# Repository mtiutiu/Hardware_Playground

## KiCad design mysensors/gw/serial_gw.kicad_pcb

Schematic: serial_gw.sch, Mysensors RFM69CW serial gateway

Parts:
C1, C2, C3, C4, C6, C7, C9, C12, C14: 100n; C_0603_HandSoldering
C8, C10, C11: 1u; C_0603_HandSoldering
C13: 22u; C_0603_HandSoldering
CON1: AVR-ISP-6; AVR_ISP_SMT_Small_02x03
D1: RX; LED_0603
D2: TX; LED_0603
D3: ERR; LED_0603
IC1: ATMEGA328P-MU; QFN-32-1EP_5x5mm_Pitch0.5mm
P1: USB_A
P2: ANTENNA; Pin_Header_Straight_1x01_Pitch2.00mm
R1: 10K; R_0603_HandSoldering
R2, R3, R4: 330; R_0603_HandSoldering
R5: 56K; R_0603_HandSoldering
R6: 1K; R_0603_HandSoldering
SW1: RESET; SW_SPST_EVQPE1
U1: TXB0104; TSSOP-14_4.4x5mm_Pitch0.65mm
U2: MCP1703A-3302; SOT89-3_Housing
U3: CP2102; QFN-28-1EP_5x5mm_Pitch0.5mm
U4: RFM69W; RFM69HW_SMD_Handsoldering
U5: ATSHA204A; SOT-23
X1: 16MHz; ZTTCS-3

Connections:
+3V3: C9.2, C11.1, C13.1, R5.2, U1.1, U1.8, U2.3, U4.8 (3.3V)
+5V: C1.1, C2.2, C3.2, C7.1, C8.1, C10.2, C14.1, CON1.2, IC1.4, IC1.6, IC1.18, P1.1, R1.1, R6.2, U1.14, U2.2, U3.7, U3.8, U5.2
/ATSHA204A: IC1.26, R6.1, U5.1
/DTR: C6.2, U3.28
/GW_ERR_LED: IC1.25, R4.2
/GW_RX_LED: IC1.23, R2.2
/GW_TX_LED: IC1.24, R3.2
/MISO: CON1.1, IC1.16, U1.11
/MOSI: CON1.4, IC1.15, U1.12
/RFM69W_INT: IC1.32, U4.2 (DIO0)
/RFM69W_SS: IC1.14, U1.13
/RST: C6.1, CON1.5, IC1.29, R1.2, SW1.1
/SCK: CON1.3, IC1.17, U1.10
/SER_RX: IC1.31, U3.25
/SER_TX: IC1.30, U3.26
GND: C1.2, C2.1, C3.1, C4.1, C7.2, C8.2, C9.1, C10.1, C11.2, C12.2, C13.2, C14.2, CON1.6, D1.1, D2.1, D3.1, IC1.3, IC1.5, IC1.21, P1.4, P1.5, SW1.2, U1.7, U2.1, U3.3, U4.9 (GND), U4.11 (GND), U5.3, X1.2
unnamed: C4.2, IC1.20
unnamed: C12.1, U3.6
unnamed: D1.2, R2.1
unnamed: D2.2, R3.1
unnamed: D3.2, R4.1
unnamed: IC1.7, X1.3
unnamed: IC1.8, X1.1
unnamed: P1.2, U3.5
unnamed: P1.3, U3.4
unnamed: P2.1, U4.10 (ANA)
unnamed: R5.1, U1.2, U4.15 (NSS)
unnamed: U1.3, U4.14 (MOSI)
unnamed: U1.4, U4.13 (MISO)
unnamed: U1.5, U4.12 (SCK)

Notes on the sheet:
Usb to serial converter
RFM69W radio module
3.3V supply
AVR ISP
LED panel
MCU unit
Signing module

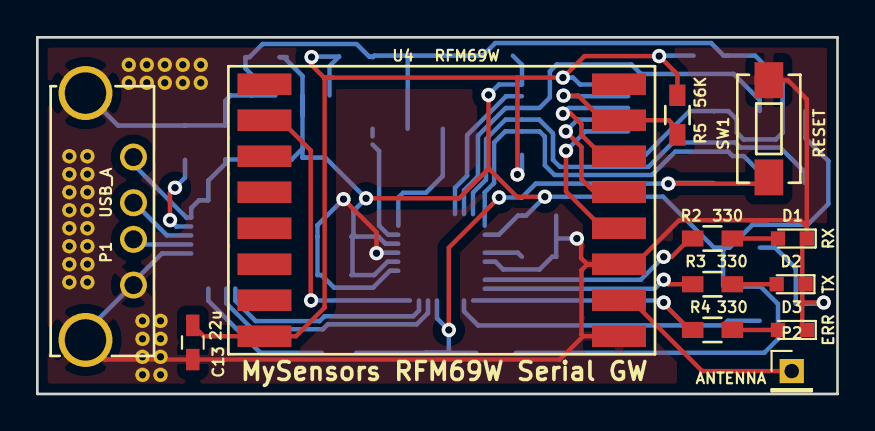
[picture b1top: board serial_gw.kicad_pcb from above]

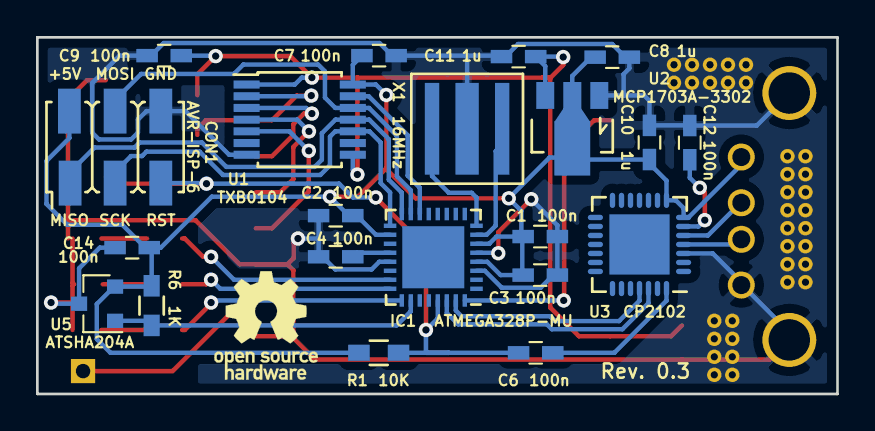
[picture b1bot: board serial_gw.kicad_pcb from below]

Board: 2 copper layers, 44.5 x 19.8 mm, 33 parts (21 on the bottom side), 30 nets.

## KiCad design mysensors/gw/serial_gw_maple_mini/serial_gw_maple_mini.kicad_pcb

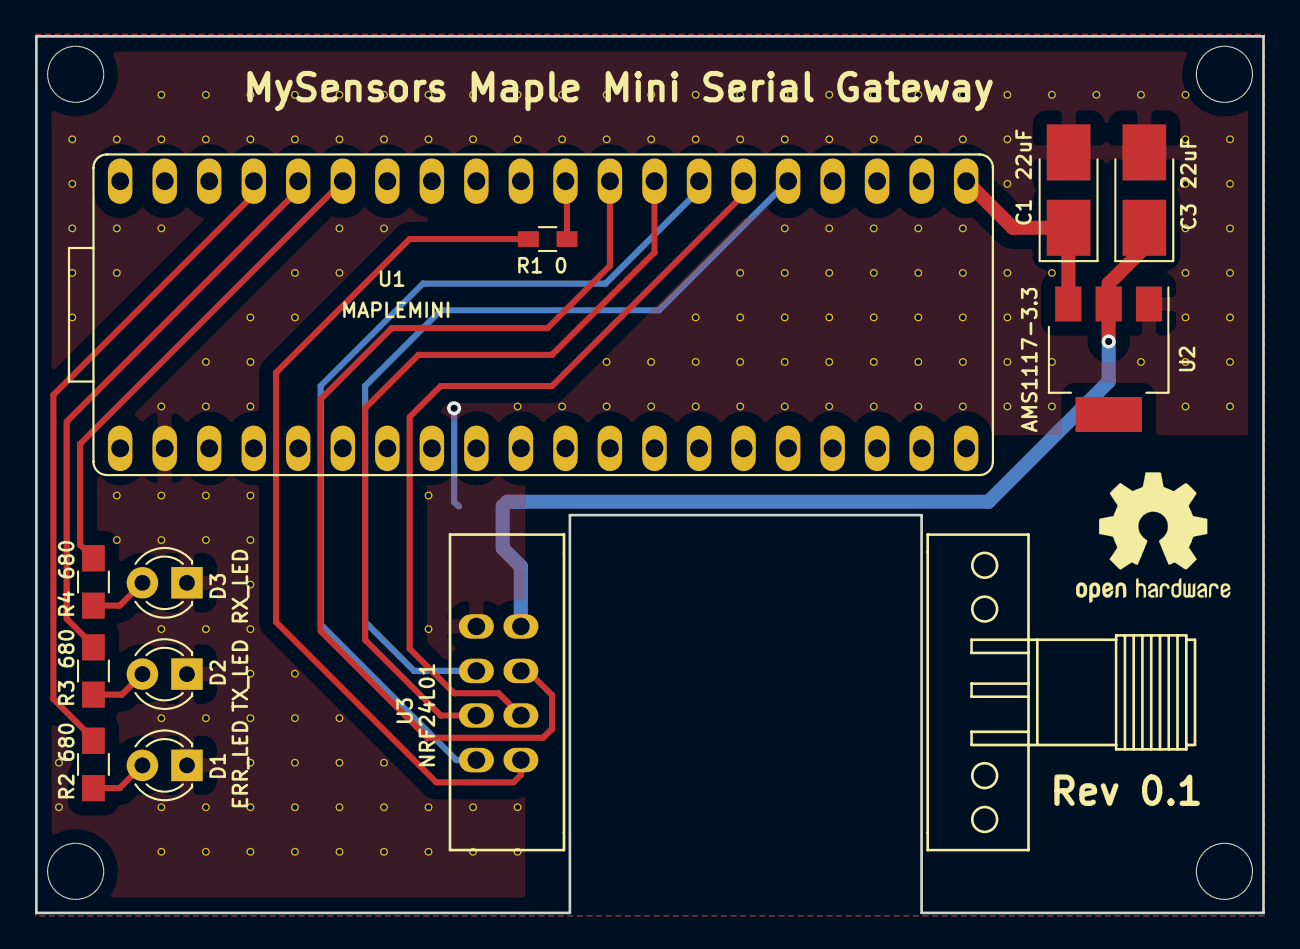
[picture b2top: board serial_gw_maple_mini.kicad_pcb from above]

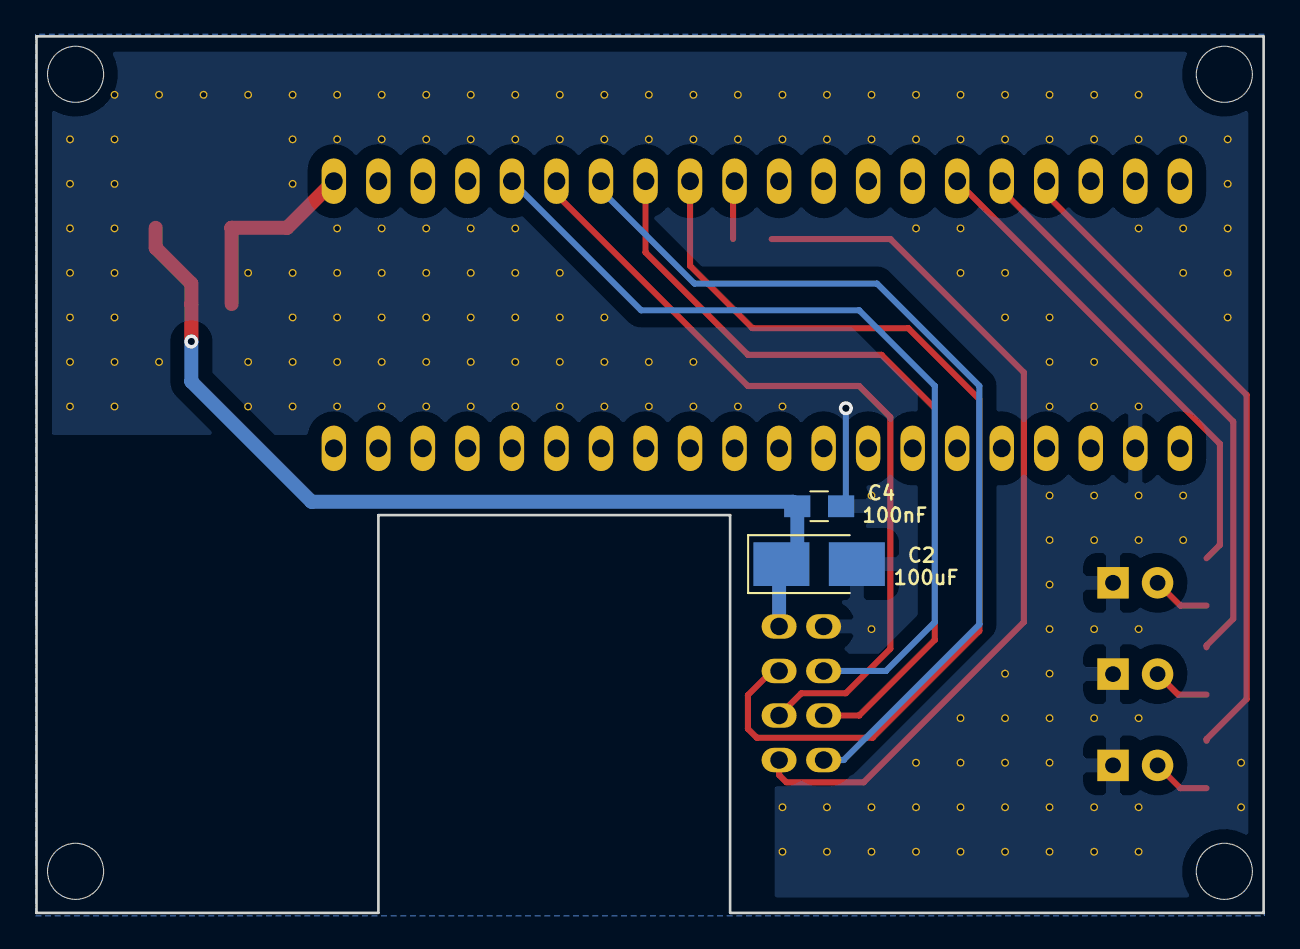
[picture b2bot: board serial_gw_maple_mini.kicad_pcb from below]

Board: 2 copper layers, 70.0 x 50.0 mm, 184 parts (2 on the bottom side), 16 nets.

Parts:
C1, C3: 22uF; CP_Tantalum_Case-B_EIA-3528-21_Hand
C2: 100uF; CP_Tantalum_Case-B_EIA-3528-21_Hand
C4: 100nF; C_0805_HandSoldering
D1: ERR_LED; LED_D3.0mm
D2: TX_LED; LED_D3.0mm
D3: RX_LED; LED_D3.0mm
R1: 0; R_0603_HandSoldering
R2, R3, R4: 680; R_0805_HandSoldering
U1: MAPLEMINI; MAPLE_MINI
U2: AMS1117-3.3; SOT-223
U3: NRF24L01; E01-ML01DP5
V3_4, V3_5, V3_6, V3_7, V3_8, V3_18, V3_19, V4_4, V4_6, V4_7, V4_12, V4_13, V5_3, V5_4, V5_6, V5_10, V5_12, V5_13, V5_15, V5_17, V5_19, V5_20, V6_3, V6_4, V6_9, V6_10, V6_12, V6_13, V6_15, V6_17, V6_19, V6_20, V7_3, V7_4, V7_8, V7_9, V7_10, V7_12, V7_13, V7_14, V7_15, V7_16, V7_17, V7_18, V7_19, V7_20, V8_3, V8_4, V8_7, V8_8, V8_16, V8_17, V8_18, V8_19, V8_20, V9_3, V9_4, V9_6, V9_7, V9_17, V9_18, V9_19, V9_20, V10_3, V10_4, V10_6, V10_18, V10_19, V10_20, V11_3, V11_4, V11_12, V11_15, V11_19, V11_20, V12_3, V12_4, V12_19, V12_20, V13_3, V13_4, V13_10, V13_19, V13_20, V14_3, V14_4, V14_10, V15_3, V15_4, V15_9, V15_10, V16_3, V16_4, V16_9, V16_10, V17_3, V17_4, V17_8, V17_9, V17_10, V18_3, V18_4, V18_7, V18_8, V18_9, V18_10, V19_3, V19_4, V19_6, V19_7, V19_8, V19_9, V19_10, V20_3, V20_4, V20_6, V20_7, V20_8, V20_9, V20_10, V21_3, V21_4, V21_6, V21_7, V21_8, V21_9, V21_10, V22_3, V22_4, V22_6, V22_7, V22_8, V22_9, V22_10, V23_3, V23_4, V23_6, V23_7, V23_8, V23_9, V23_10, V24_3, V24_4, V24_5, V24_7, V24_8, V24_9, V24_10, V25_3, V25_7, V25_9, V25_10, V26_3, V27_3, V27_9, V28_3, V28_4, V28_5, V28_6, V28_7, V28_8, V28_9, V28_10, V29_4, V29_5, V29_6, V29_7, V29_8, V29_9, V29_10: AUTO_VIA; VIA_MATRIX

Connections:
+3V3: C2.1, C3.1, C4.1, U2.2, U3.2
/ERR_LED: R2.2, U1.37
/MAPLE_VIN: C1.1, U1.21, U2.3
/NRF24_IRQ: R1.1, U3.8
/RX_LED: R4.2, U1.35
/SPI_CE: U1.25, U3.3
/SPI_CSN: U1.29, U3.4
/SPI_MISO: U1.27, U3.7
/SPI_MOSI: U1.26, U3.6
/SPI_SCK: U1.28, U3.5
/TX_LED: R3.2, U1.36
GND: C1.2, C2.2, C3.2, C4.2, D1.1, D2.1, D3.1, U1.2, U2.1, U3.1, V3_4.1, V3_5.1, V3_6.1, V3_7.1, V3_8.1, V3_18.1, V3_19.1, V4_4.1, V4_6.1, V4_7.1, V4_12.1, V4_13.1, V5_3.1, V5_4.1, V5_6.1, V5_10.1, V5_12.1, V5_13.1, V5_15.1, V5_17.1, V5_19.1, V5_20.1, V6_3.1, V6_4.1, V6_9.1, V6_10.1, V6_12.1, V6_13.1, V6_15.1, V6_17.1, V6_19.1, V6_20.1, V7_3.1, V7_4.1, V7_8.1, V7_9.1, V7_10.1, V7_12.1, V7_13.1, V7_14.1, V7_15.1, V7_16.1, V7_17.1, V7_18.1, V7_19.1, V7_20.1, V8_3.1, V8_4.1, V8_7.1, V8_8.1, V8_16.1, V8_17.1, V8_18.1, V8_19.1, V8_20.1, V9_3.1, V9_4.1, V9_6.1, V9_7.1, V9_17.1, V9_18.1, V9_19.1, V9_20.1, V10_3.1, V10_4.1, V10_6.1, V10_18.1, V10_19.1, V10_20.1, V11_3.1, V11_4.1, V11_12.1, V11_15.1, V11_19.1, V11_20.1, V12_3.1, V12_4.1, V12_19.1, V12_20.1, V13_3.1, V13_4.1, V13_10.1, V13_19.1, V13_20.1, V14_3.1, V14_4.1, V14_10.1, V15_3.1, V15_4.1, V15_9.1, V15_10.1, V16_3.1, V16_4.1, V16_9.1, V16_10.1, V17_3.1, V17_4.1, V17_8.1, V17_9.1, V17_10.1, V18_3.1, V18_4.1, V18_7.1, V18_8.1, V18_9.1, V18_10.1, V19_3.1, V19_4.1, V19_6.1, V19_7.1, V19_8.1, V19_9.1, V19_10.1, V20_3.1, V20_4.1, V20_6.1, V20_7.1, V20_8.1, V20_9.1, V20_10.1, V21_3.1, V21_4.1, V21_6.1, V21_7.1, V21_8.1, V21_9.1, V21_10.1, V22_3.1, V22_4.1, V22_6.1, V22_7.1, V22_8.1, V22_9.1, V22_10.1, V23_3.1, V23_4.1, V23_6.1, V23_7.1, V23_8.1, V23_9.1, V23_10.1, V24_3.1, V24_4.1, V24_5.1, V24_7.1, V24_8.1, V24_9.1, V24_10.1, V25_3.1, V25_7.1, V25_9.1, V25_10.1, V26_3.1, V27_3.1, V27_9.1, V28_3.1, V28_4.1, V28_5.1, V28_6.1, V28_7.1, V28_8.1, V28_9.1, V28_10.1, V29_4.1, V29_5.1, V29_6.1, V29_7.1, V29_8.1, V29_9.1, V29_10.1
unnamed: D1.2, R2.1
unnamed: D2.2, R3.1
unnamed: D3.2, R4.1
unnamed: R1.2, U1.30

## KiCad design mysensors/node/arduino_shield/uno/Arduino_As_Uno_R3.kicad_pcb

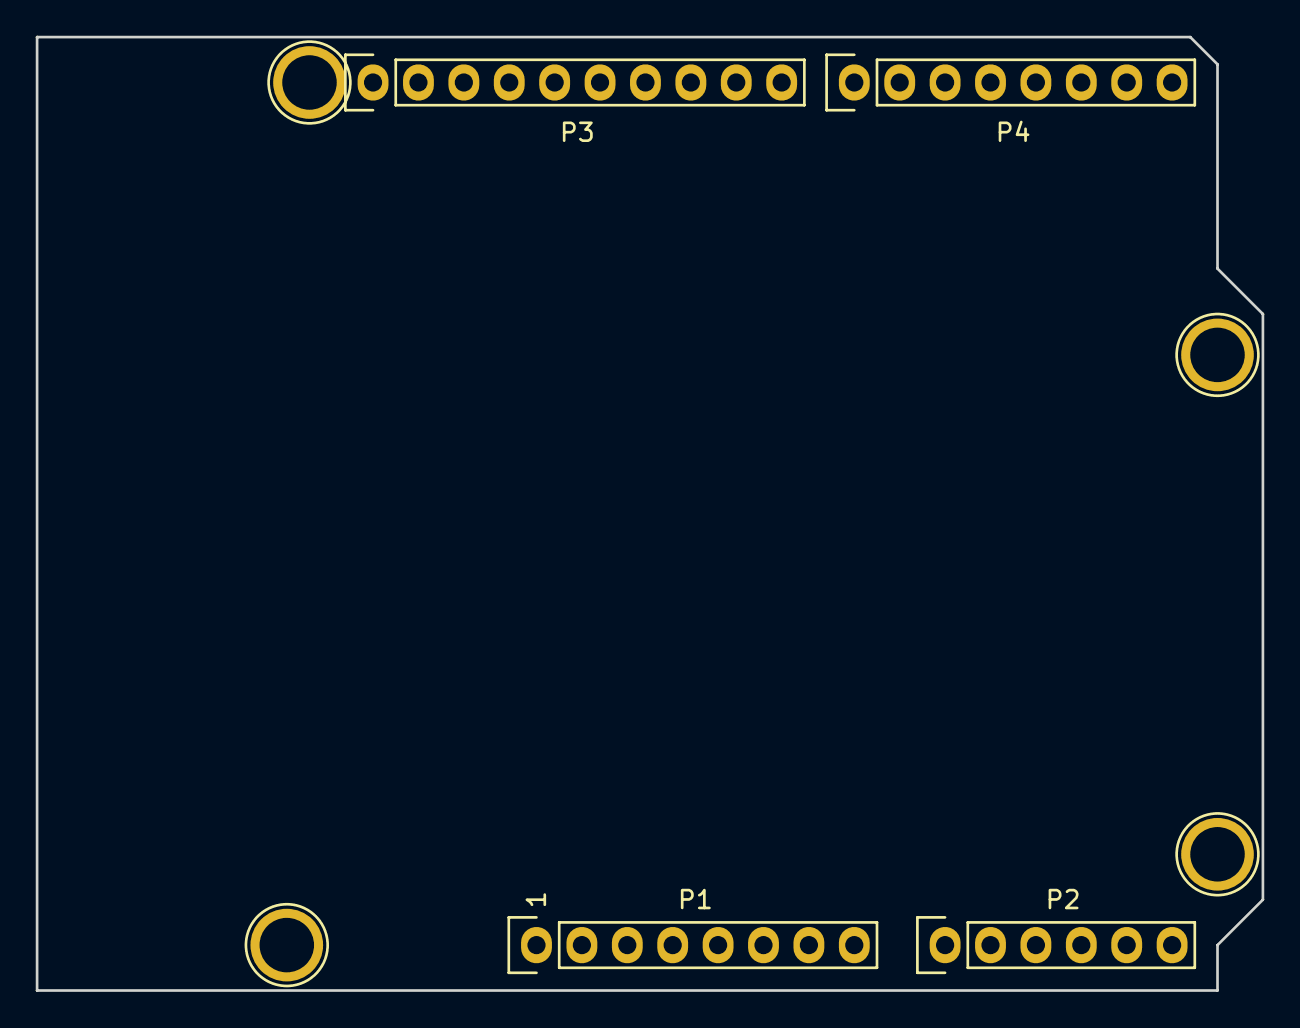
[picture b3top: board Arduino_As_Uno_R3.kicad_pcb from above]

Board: 2 copper layers, 68.6 x 53.3 mm, 8 parts (0 on the bottom side), 3 nets, no tracks yet.

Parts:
P1: Power; Socket_Strip_Arduino_1x08
P2: Analog; Socket_Strip_Arduino_1x06
P3: Digital; Socket_Strip_Arduino_1x10
P4: Digital; Socket_Strip_Arduino_1x08
P5, P6, P7, P8: CONN_01X01; Arduino_1pin

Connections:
/A4(SDA): P2.5, P3.2
/A5(SCL): P2.6, P3.1
GND: P1.6, P1.7, P3.4

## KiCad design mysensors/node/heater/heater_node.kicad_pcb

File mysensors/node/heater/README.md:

## Mysensors RFM69W heater relay module
More details here: https://www.openhardware.io/view/334/MySensors-RFM69W-relay-actuator-node

##### 3D renderings of pcb

Top view | Bottom view
------------ | -------------
 | 

**Description:**

This is a Mysensors RFM69W actuator node for controlling a heater or other appliances using a relay

**Key Features:**

 - **AT25DF512C-SSHN-B** SPI flash module for OTA
 - **ATSHA204A** for signing
 - **MySensors** ready(Atmega328p + RFM69W)
 - **HLK-PM01** as power supply

**Work progress:**

 1. Test/verify the pcb board correctness(from both electrical and mechanical point of views) - **DONE**
 2. Produce the initial PCB's using some external PCB manufacturer - **DONE**
 3. Components assembly(soldering) -**DONE**
 4. Create 3D printed plastic enclosure - **DONE**
 5. Create MySensors sketch code - **DONE**
 6. Verify the real board with running code - **DONE**

**HW Revisions:**
 - 0.1 - initial hw design
 - 0.2 - removed capacitor from reset switch as it can interfere with arduino serial bootloader if used

**Credits:**
  
  All credits go to **MySensors** team for the great work and to the opensource community

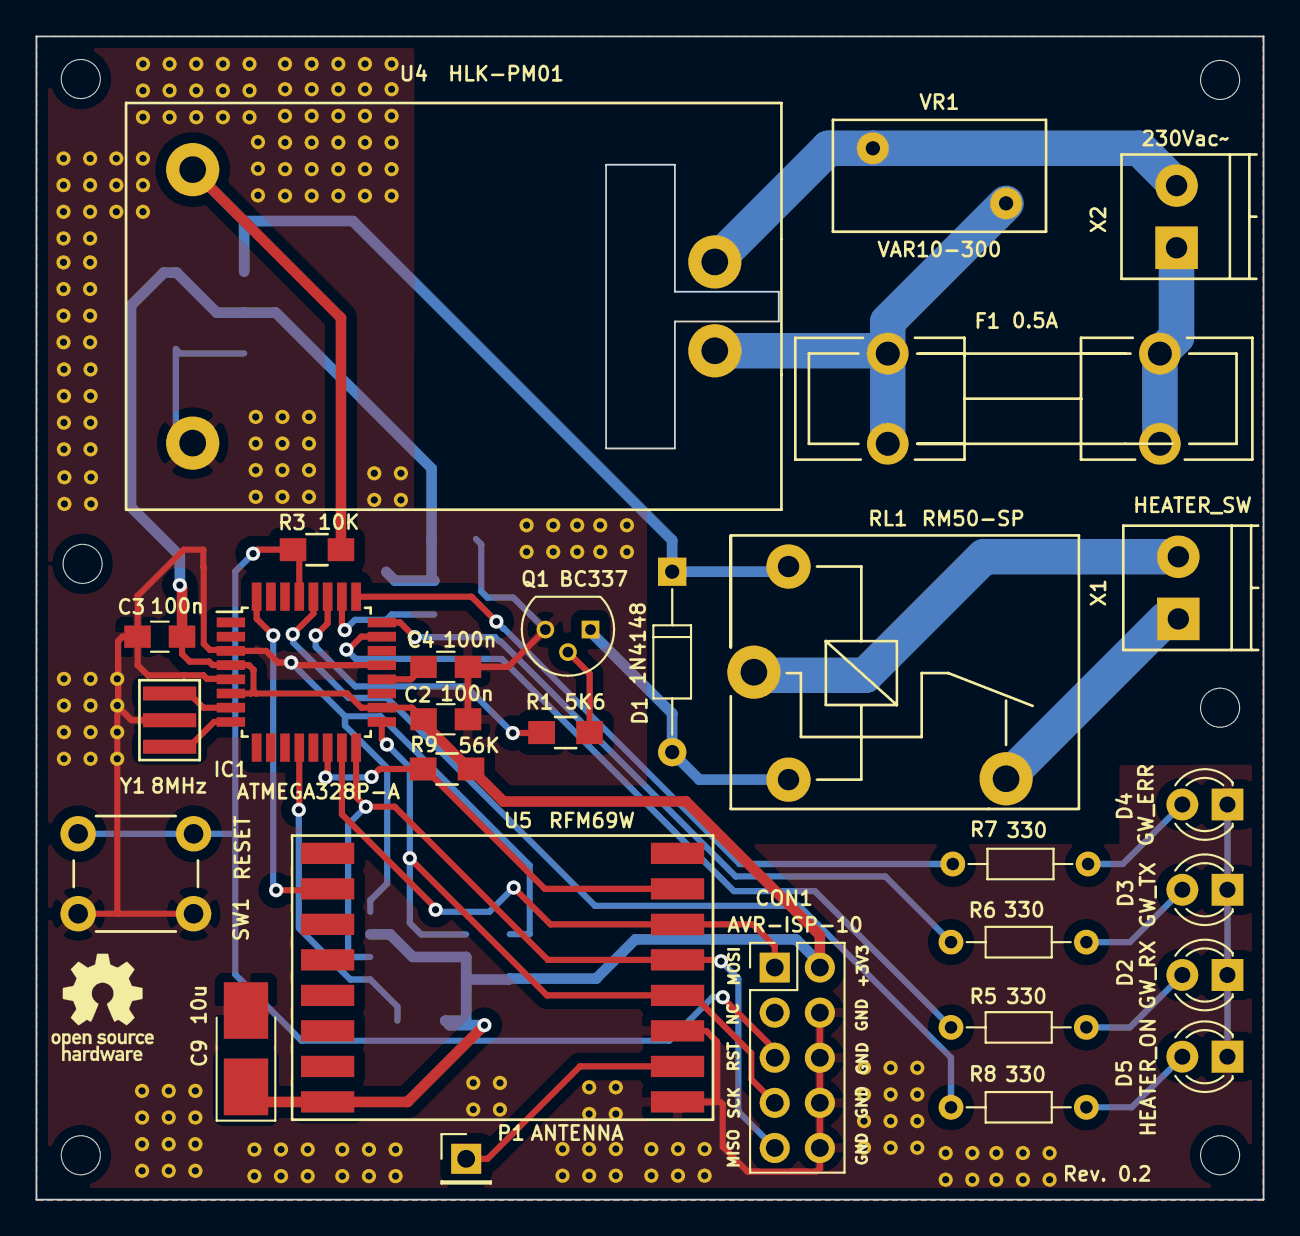
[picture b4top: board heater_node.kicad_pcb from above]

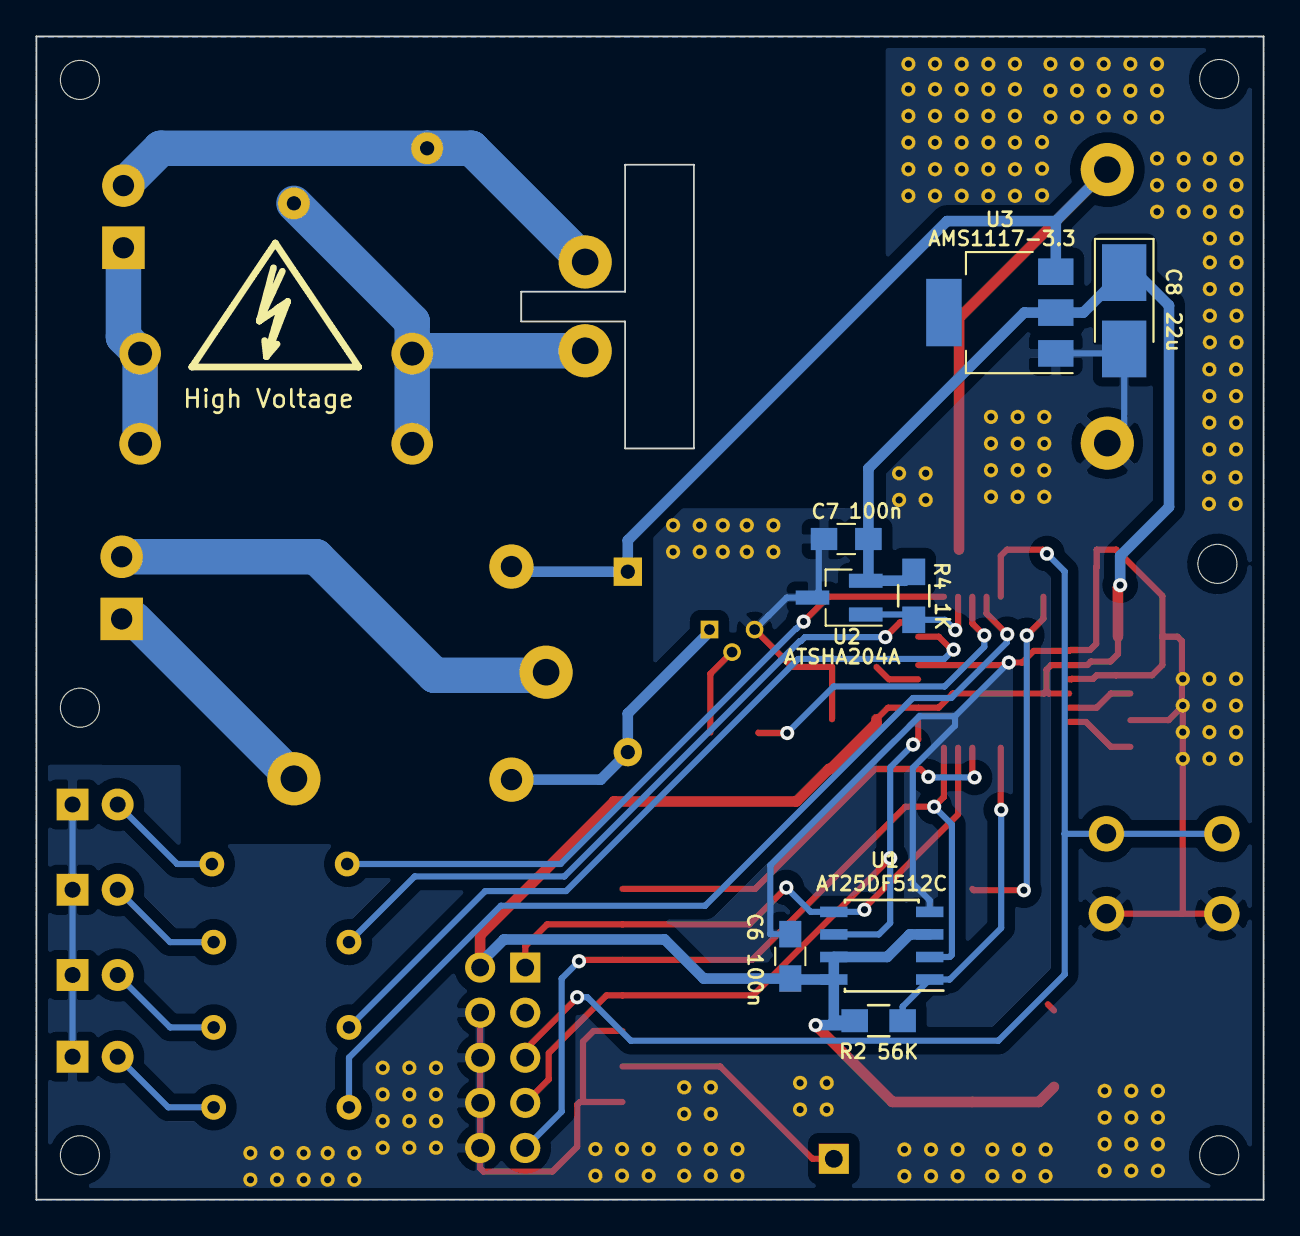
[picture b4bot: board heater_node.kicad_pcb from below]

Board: 2 copper layers, 69.1 x 65.5 mm, 37 parts (8 on the bottom side), 31 nets.

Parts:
C2, C3, C4, C6, C7: 100n; C_0805_HandSoldering
C8: 22u; CP_Tantalum_Case-B_EIA-3528-21_Hand
C9: 10u; CP_Tantalum_Case-B_EIA-3528-21_Hand
CON1: AVR-ISP-10; Pin_Header_Straight_2x05_Pitch2.54mm
D1: 1N4148; D_DO-35_SOD27_P10.16mm_Horizontal
D2: GW_RX; LED_D3.0mm
D3: GW_TX; LED_D3.0mm
D4: GW_ERR; LED_D3.0mm
D5: HEATER_ON; LED_D3.0mm
F1: 0.5A; Fuseholder5x20_horiz_open_lateral_Type-II
IC1: ATMEGA328P-A; TQFP-32_7x7mm_Pitch0.8mm
P1: ANTENNA; Pin_Header_Straight_1x01_Pitch2.54mm
Q1: BC337; TO-92_Molded_Narrow
R1: 5K6; R_0805_HandSoldering
R2, R9: 56K; R_0805_HandSoldering
R3: 10K; R_0805_HandSoldering
R4: 1K; R_0805_HandSoldering
R5, R6, R7, R8: 330; R_Axial_DIN0204_L3.6mm_D1.6mm_P7.62mm_Horizontal
RL1: RM50-SP; RM50_SP
SW1: RESET; SW_PUSH_6mm
U1: AT25DF512C; SOIC-8_3.9x4.9mm_Pitch1.27mm
U2: ATSHA204A; SOT-23_Handsoldering
U3: AMS1117-3.3; SOT-223
U4: HLK-PM01
U5: RFM69W; RFM69HW_SMD_Handsoldering
VR1: VAR10-300; RV_Disc_D12_W6.3_P7.5
X1: HEATER_SW; TerminalBlock_Pheonix_PT-3.5mm_2pol
X2: 230Vac~~; TerminalBlock_Pheonix_PT-3.5mm_2pol
Y1: 8MHz; ZTTCR-3

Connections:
+3V3: C2.2, C3.2, C6.1, C7.1, C8.1, C9.1, CON1.2, IC1.4, IC1.6, IC1.18, R2.2, R4.2, R9.2, U1.3, U1.7, U1.8, U2.2, U3.2, U5.8
+5V: D1.1, R3.1, RL1.A1, U3.3, U4.3
/ATSHA204A: IC1.26, R4.1, U2.1
/ERR_LED: IC1.25, R7.2
/HEATER_ON_LED: IC1.28, R8.2
/H_RELAY_CMD: IC1.27, R1.2
/MISO: CON1.9, IC1.16, U1.2, U5.13
/MOSI: CON1.1, IC1.15, U1.5, U5.14
/RFM69W_INT: IC1.32, U5.2
/RFM69W_SS: IC1.14, R9.1, U5.15
/RST: CON1.5, IC1.29, R3.2, SW1.1
/RX_LED: IC1.23, R5.2
/SCK: CON1.7, IC1.17, U1.6, U5.12
/SPI_FLASH_SS: IC1.12, R2.1, U1.1
/TX_LED: IC1.24, R6.2
GND: C2.1, C3.1, C4.1, C6.2, C7.2, C8.2, C9.2, CON1.4, CON1.6, CON1.8, CON1.10, D2.1, D3.1, D4.1, D5.1, IC1.3, IC1.5, IC1.21, Q1.3, SW1.2, U1.4, U2.3, U3.1, U4.4, U5.9, U5.11, Y1.2
unnamed: C4.2, IC1.20
unnamed: D1.2, Q1.1, RL1.A2
unnamed: D2.2, R5.1
unnamed: D3.2, R6.1
unnamed: D4.2, R7.1
unnamed: D5.2, R8.1
unnamed: F1.1, U4.1, VR1.1
unnamed: F1.2, X2.1
unnamed: IC1.7, Y1.3
unnamed: IC1.8, Y1.1
unnamed: P1.1, U5.10
unnamed: Q1.2, R1.1
unnamed: RL1.11, X1.2
unnamed: RL1.14, X1.1
unnamed: U4.2, VR1.2, X2.2

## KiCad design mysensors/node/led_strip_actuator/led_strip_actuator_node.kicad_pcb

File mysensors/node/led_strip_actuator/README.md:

## Mysensors RFM69W LED strip relay module

##### 3D renderings of pcb

Top view | Bottom view
------------ | -------------
 | 

**Description:**

This is a Mysensors RFM69W actuator node for controlling a 12V LED strip using a relay

**Key Features:**

 - **AT25DF512C-SSHN-B** SPI flash module for OTA
 - **ATSHA204A** for signing
 - **MySensors** ready(Atmega328p + RFM69W)

**Work progress:**

 1. Test/verify the pcb board correctness(from both electrical and mechanical point of views) - **IN PROGRESS**
 2. Produce the initial PCB's using some external PCB manufacturer
 3. Components assembly(soldering)
 4. Create 3D printed plastic enclosure
 5. Create MySensors sketch code
 6. Verify the real board with running code

**Note: Work in progress(schematic/pcb will change).**

**HW Revisions:**
 - 0.1 - initial hw design

**Credits:**
  
  All credits go to **MySensors** team for the great work and to the opensource community

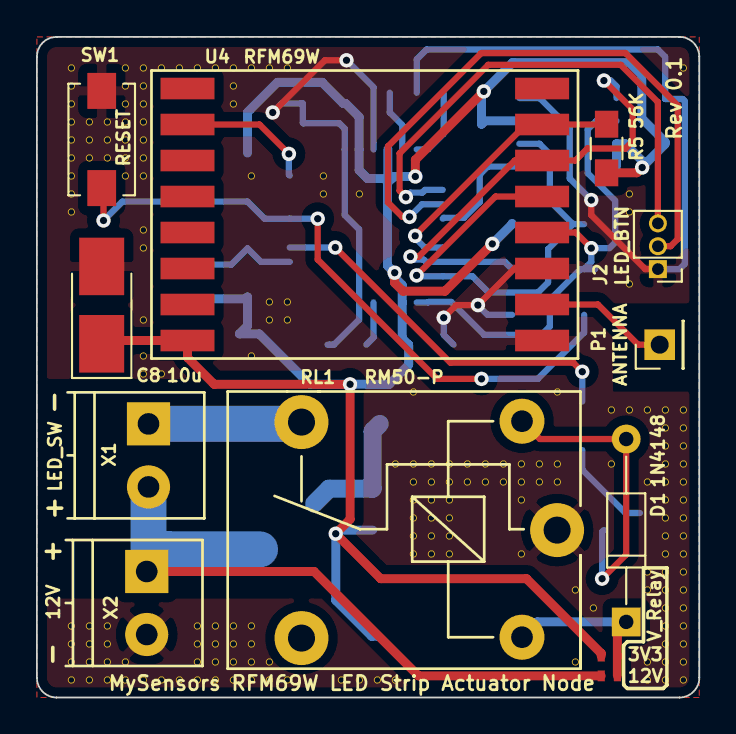
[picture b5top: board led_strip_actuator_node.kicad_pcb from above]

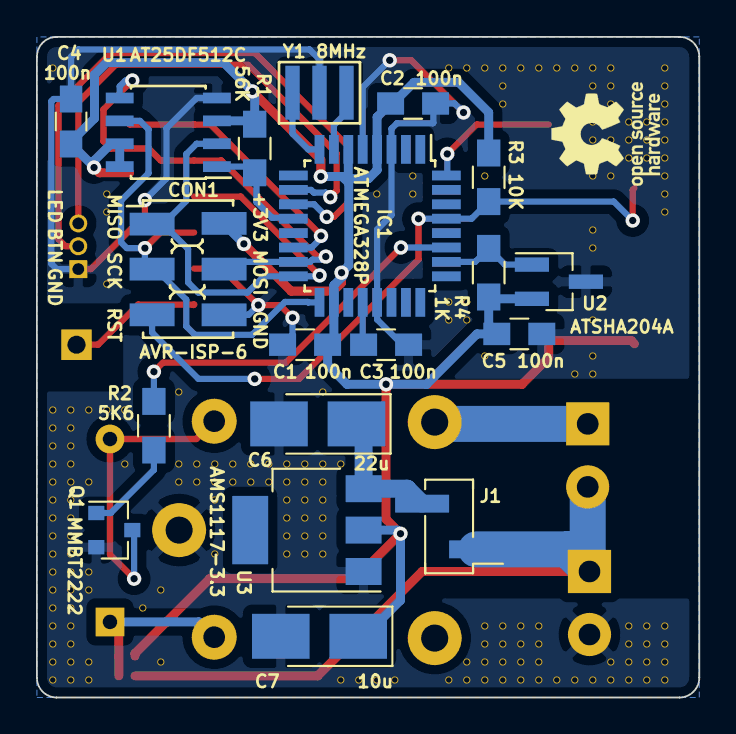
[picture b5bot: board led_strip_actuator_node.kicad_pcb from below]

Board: 2 copper layers, 36.8 x 36.7 mm, 208 parts (19 on the bottom side), 23 nets.

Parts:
C1, C2, C3, C4, C5: 100n; C_0805_HandSoldering
C6: 22u; CP_Tantalum_Case-B_EIA-3528-21_Hand
C7, C8: 10u; CP_Tantalum_Case-B_EIA-3528-21_Hand
CON1: AVR-ISP-6; AVR_ISP_SMT_Small_02x03
D1: 1N4148; D_DO-35_SOD27_P10.16mm_Horizontal
IC1: ATMEGA328P; TQFP-32_7x7mm_Pitch0.8mm
J1: EXT_DC_DC; Pin_Header_Straight_1x02_Pitch2.54mm_SMD_Pin1Left
J2: LED_BTN; Pin_Header_Straight_1x03_Pitch1.27mm
JP1: 3V3; R_0402_NoSilk
JP2: 12V; R_0402_NoSilk
P1: ANTENNA; Pin_Header_Straight_1x01_Pitch2.54mm
Q1: MMBT2222; SOT-23
R1, R5: 56K; R_0805_HandSoldering
R2: 5K6; R_0805_HandSoldering
R3: 10K; R_0805_HandSoldering
R4: 1K; R_0805_HandSoldering
RL1: RM50-P; RM50_P
SW1: RESET; SW_SPST_EVQPE1
U1: AT25DF512C; SOIC-8_3.9x4.9mm_Pitch1.27mm
U2: ATSHA204A; SOT-23_Handsoldering
U3: AMS1117-3.3; SOT-223
U4: RFM69W; RFM69HW_SMD_Handsoldering
V2_10, V2_11, V2_12, V2_13, V2_14, V2_15, V2_16, V2_17, V2_18, V2_41, V2_42, V2_43, V2_44, V3_13, V3_14, V3_15, V3_41, V3_42, V3_43, V3_44, V4_13, V4_14, V4_15, V4_41, V4_42, V4_43, V4_44, V5_10, V5_11, V5_12, V5_13, V5_14, V5_15, V5_16, V5_43, V5_44, V6_10, V6_11, V6_12, V6_13, V6_14, V6_15, V6_16, V6_19, V6_20, V6_24, V6_26, V6_27, V6_44, V7_10, V7_27, V7_44, V8_10, V8_44, V9_10, V9_41, V9_42, V9_43, V9_44, V10_10, V10_41, V10_42, V10_43, V10_44, V11_10, V11_11, V11_12, V11_41, V11_42, V11_43, V11_44, V12_10, V12_16, V12_26, V12_41, V12_42, V12_43, V12_44, V13_10, V13_23, V13_24, V13_43, V13_44, V14_10, V14_23, V14_24, V14_44, V16_16, V16_17, V17_44, V18_17, V18_44, V19_44, V20_32, V20_44, V21_28, V21_32, V21_33, V21_34, V21_35, V21_36, V21_37, V22_32, V22_33, V22_34, V22_35, V22_36, V22_37, V23_32, V23_33, V23_34, V23_35, V23_36, V23_37, V24_32, V24_33, V25_32, V25_33, V26_32, V26_33, V27_32, V27_33, V27_34, V27_37, V28_32, V28_33, V29_28, V29_32, V29_33, V30_39, V30_43, V31_40, V32_29, V32_32, V33_17, V33_18, V33_22, V33_29, V34_29, V34_33, V34_38, V34_39, V34_43, V34_44, V35_29, V35_30, V35_31, V35_32, V35_33, V35_34, V35_35, V35_36, V35_37, V35_38, V35_39, V35_40, V35_41, V35_42, V35_43, V35_44, V36_10, V36_29, V36_30, V36_31, V36_32, V36_33, V36_34, V36_35, V36_36, V36_37, V36_38, V36_39, V36_40, V36_41, V36_42, V36_43, V36_44: AUTO_VIA; VIA_MATRIX
X1: LED_SW; TerminalBlock_Pheonix_PT-3.5mm_2pol
X2: 12V; TerminalBlock_Pheonix_PT-3.5mm_2pol
Y1: 8MHz; ZTTCR-3

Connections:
+3V3: C1.2, C2.2, C4.1, C5.1, C7.1, C8.1, CON1.2, IC1.4, IC1.6, IC1.18, JP1.1, R1.2, R3.1, R4.2, R5.2, U1.3, U1.7, U1.8, U2.2, U3.2, U4.8
/ATSHA204A: IC1.26, R4.1, U2.1
/LED_12V: J1.1, JP2.2, X1.2, X2.1
/LED_BTN: IC1.11, J2.2
/LED_BTN_SIGNALING: IC1.10, J2.3
/LED_RELAY_CMD: IC1.27, R2.2
/MISO: CON1.1, IC1.16, U1.2, U4.13
/MOSI: CON1.4, IC1.15, U1.5, U4.14
/RFM69W_INT: IC1.32, U4.2
/RFM69W_SS: IC1.14, R5.1, U4.15
/RST: CON1.5, IC1.29, R3.2, SW1.1
/SCK: CON1.3, IC1.17, U1.6, U4.12
/SPI_FLASH_SS: IC1.12, R1.1, U1.1
GND: C1.1, C2.1, C3.1, C4.2, C5.2, C6.2, C7.2, C8.2, CON1.6, IC1.3, IC1.5, IC1.21, J2.1, Q1.2, RL1.11, SW1.2, U1.4, U2.3, U3.1, U4.9, U4.11, V2_10.1, V2_11.1, V2_12.1, V2_13.1, V2_14.1, V2_15.1, V2_16.1, V2_17.1, V2_18.1, V2_41.1, V2_42.1, V2_43.1, V2_44.1, V3_13.1, V3_14.1, V3_15.1, V3_41.1, V3_42.1, V3_43.1, V3_44.1, V4_13.1, V4_14.1, V4_15.1, V4_41.1, V4_42.1, V4_43.1, V4_44.1, V5_10.1, V5_11.1, V5_12.1, V5_13.1, V5_14.1, V5_15.1, V5_16.1, V5_43.1, V5_44.1, V6_10.1, V6_11.1, V6_12.1, V6_13.1, V6_14.1, V6_15.1, V6_16.1, V6_19.1, V6_20.1, V6_24.1, V6_26.1, V6_27.1, V6_44.1, V7_10.1, V7_27.1, V7_44.1, V8_10.1, V8_44.1, V9_10.1, V9_41.1, V9_42.1, V9_43.1, V9_44.1, V10_10.1, V10_41.1, V10_42.1, V10_43.1, V10_44.1, V11_10.1, V11_11.1, V11_12.1, V11_41.1, V11_42.1, V11_43.1, V11_44.1, V12_10.1, V12_16.1, V12_26.1, V12_41.1, V12_42.1, V12_43.1, V12_44.1, V13_10.1, V13_23.1, V13_24.1, V13_43.1, V13_44.1, V14_10.1, V14_23.1, V14_24.1, V14_44.1, V16_16.1, V16_17.1, V17_44.1, V18_17.1, V18_44.1, V19_44.1, V20_32.1, V20_44.1, V21_28.1, V21_32.1, V21_33.1, V21_34.1, V21_35.1, V21_36.1, V21_37.1, V22_32.1, V22_33.1, V22_34.1, V22_35.1, V22_36.1, V22_37.1, V23_32.1, V23_33.1, V23_34.1, V23_35.1, V23_36.1, V23_37.1, V24_32.1, V24_33.1, V25_32.1, V25_33.1, V26_32.1, V26_33.1, V27_32.1, V27_33.1, V27_34.1, V27_37.1, V28_32.1, V28_33.1, V29_28.1, V29_32.1, V29_33.1, V30_39.1, V30_43.1, V31_40.1, V32_29.1, V32_32.1, V33_17.1, V33_18.1, V33_22.1, V33_29.1, V34_29.1, V34_33.1, V34_38.1, V34_39.1, V34_43.1, V34_44.1, V35_29.1, V35_30.1, V35_31.1, V35_32.1, V35_33.1, V35_34.1, V35_35.1, V35_36.1, V35_37.1, V35_38.1, V35_39.1, V35_40.1, V35_41.1, V35_42.1, V35_43.1, V35_44.1, V36_10.1, V36_29.1, V36_30.1, V36_31.1, V36_32.1, V36_33.1, V36_34.1, V36_35.1, V36_36.1, V36_37.1, V36_38.1, V36_39.1, V36_40.1, V36_41.1, V36_42.1, V36_43.1, V36_44.1, X2.2, Y1.2
unnamed: C3.2, IC1.20
unnamed: C6.1, J1.2, U3.3
unnamed: D1.1, JP1.2, JP2.1, RL1.A1
unnamed: D1.2, Q1.3, RL1.A2
unnamed: IC1.7, Y1.3
unnamed: IC1.8, Y1.1
unnamed: P1.1, U4.10
unnamed: Q1.1, R2.1
unnamed: RL1.14, X1.1
